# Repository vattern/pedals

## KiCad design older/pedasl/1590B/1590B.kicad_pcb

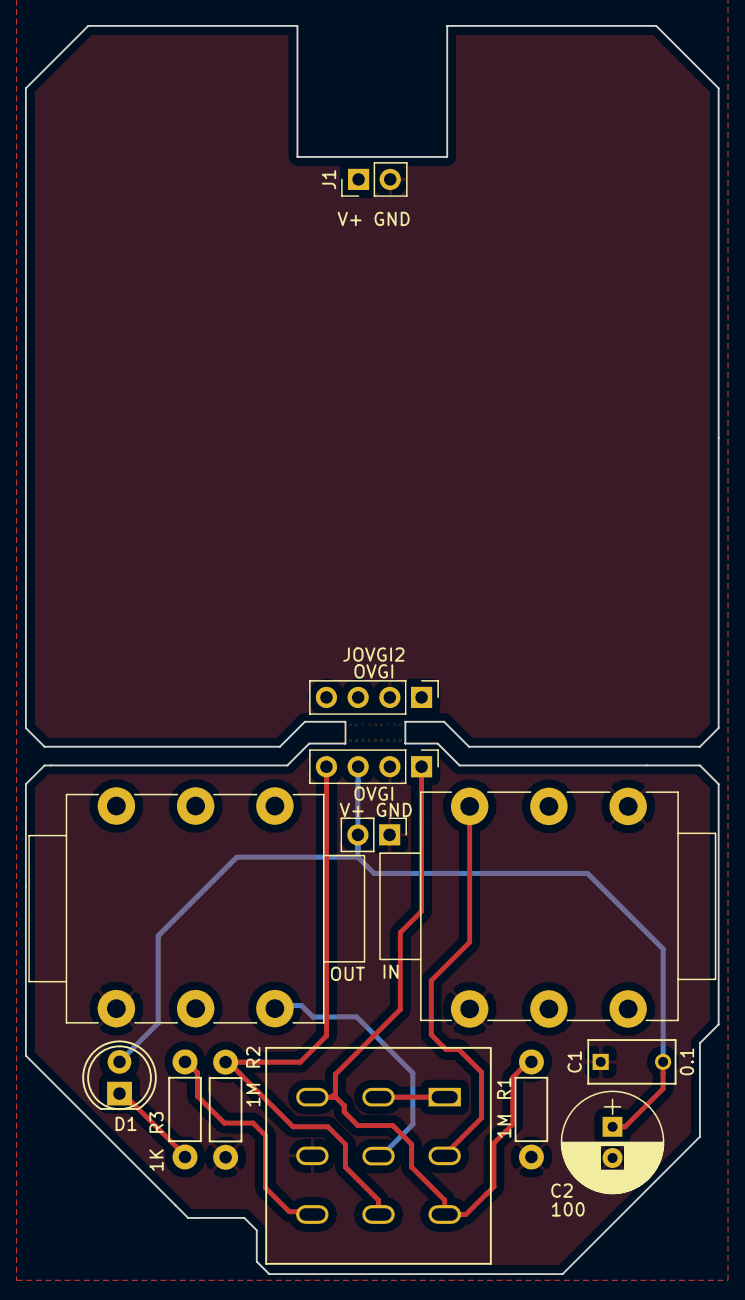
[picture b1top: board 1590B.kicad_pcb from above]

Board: 2 copper layers, 55.5 x 100.0 mm, 13 parts (0 on the bottom side), 9 nets.

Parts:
C1: 0.1; C_Rect_L7_W3.5_P5
C2: 100; CP_Radial_D8.0mm_P2.50mm
D1: LED; LED-5MM
J1, J4: V+ GND; Pin_Header_Straight_1x02_Pitch2.54mm
J2: IN; NMJ6HCD2
J3: OUT; NMJ6HCD2
JOVGI1, JOVGI2: OVGI; Pin_Header_Straight_1x04_Pitch2.54mm
R1, R2: 1M; Resistor_Horizontal_RM7mm
R3: 1K; Resistor_Horizontal_RM7mm
SW1: SW_3PDT; 3PDT-Footswitch

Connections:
+9V: C1.2, C2.1, D1.2, J1.1, J4.2, JOVGI1.3, JOVGI2.3
/I: JOVGI1.1, JOVGI2.1, R1.1, SW1.3, SW1.7
/O: JOVGI1.4, JOVGI2.4, R2.1, SW1.8
GND: C1.1, C2.2, J1.2, J2.1, J2.5, J3.1, J4.1, JOVGI1.2, JOVGI2.2, R1.2, R2.2, SW1.6
unnamed: D1.1, R3.1
unnamed: J2.2, SW1.4
unnamed: J3.2, SW1.5
unnamed: R3.2, SW1.9
unnamed: SW1.1, SW1.2

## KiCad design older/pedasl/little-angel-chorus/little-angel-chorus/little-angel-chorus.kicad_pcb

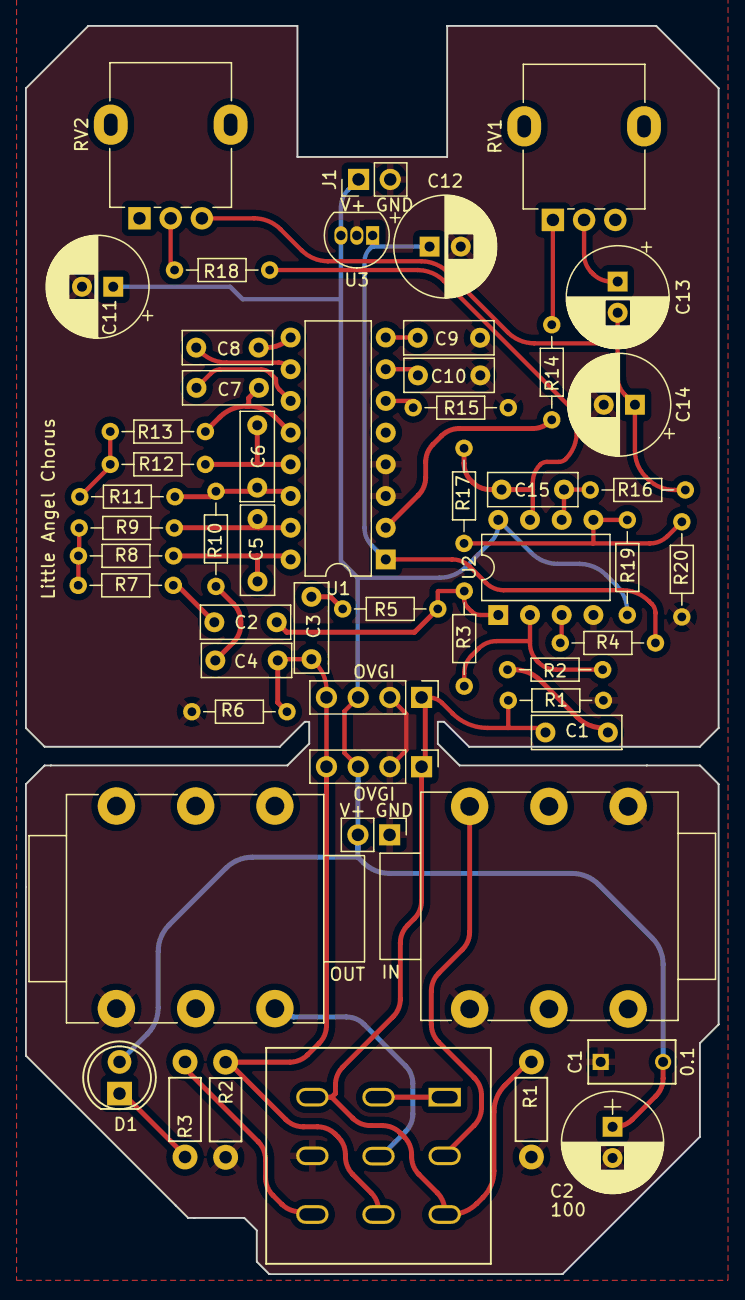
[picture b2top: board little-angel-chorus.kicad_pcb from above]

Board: 2 copper layers, 55.5 x 100.0 mm, 53 parts (0 on the bottom side), 38 nets.

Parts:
C1: 0.1; C_Rect_L7_W3.5_P5
C1#2, C2, C3, C4, C9, C10: 100nF; C_Disc_D7.0mm_W2.5mm_P5.00mm
C2#2: 100; CP_Radial_D8.0mm_P2.50mm
C5, C6: 1nF; C_Disc_D7.0mm_W2.5mm_P5.00mm
C7, C8, C15: 10nF; C_Disc_D7.0mm_W2.5mm_P5.00mm
C11: 100uF; CP_Radial_D8.0mm_P2.50mm
C12: 47uF; CP_Radial_D8.0mm_P2.50mm
C13, C14: 10uF; CP_Radial_D8.0mm_P2.50mm
D1: LED; LED-5MM
J1, J4: V+ GND; Pin_Header_Straight_1x02_Pitch2.54mm
J2: IN; NMJ6HCD2
J3: OUT; NMJ6HCD2
JOVGI1, JOVGI2: OVGI; Pin_Header_Straight_1x04_Pitch2.54mm
R1, R2: 1M; Resistor_Horizontal_RM7mm
R1#2, R3: 1M; R_Axial_DIN0204_L3.6mm_D1.6mm_P7.62mm_Horizontal
R2#2: 470k; R_Axial_DIN0204_L3.6mm_D1.6mm_P7.62mm_Horizontal
R3#2: 1K; Resistor_Horizontal_RM7mm
R4: 330k; R_Axial_DIN0204_L3.6mm_D1.6mm_P7.62mm_Horizontal
R5, R7, R8, R9, R10, R11, R12, R13: 10k; R_Axial_DIN0204_L3.6mm_D1.6mm_P7.62mm_Horizontal
R6, R19: 100k; R_Axial_DIN0204_L3.6mm_D1.6mm_P7.62mm_Horizontal
R14: 33k; R_Axial_DIN0204_L3.6mm_D1.6mm_P7.62mm_Horizontal
R15: 100R; R_Axial_DIN0204_L3.6mm_D1.6mm_P7.62mm_Horizontal
R16: 220K; R_Axial_DIN0204_L3.6mm_D1.6mm_P7.62mm_Horizontal
R17: 220k; R_Axial_DIN0204_L3.6mm_D1.6mm_P7.62mm_Horizontal
R18: 4k7; R_Axial_DIN0204_L3.6mm_D1.6mm_P7.62mm_Horizontal
R20: 47k; R_Axial_DIN0204_L3.6mm_D1.6mm_P7.62mm_Horizontal
RV1: 470K lin; Potentiometer_Alpha_RD901F-40-00D_Single_Vertical
RV2: 100k lin; Potentiometer_Alpha_RD901F-40-00D_Single_Vertical
SW1: SW_3PDT; 3PDT-Footswitch
U1: PT2399; DIP-16_W7.62mm
U2: NE5532; DIP-8_W7.62mm
U3: L78L05_TO92; TO-92_Inline

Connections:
+9V: C1.2, C2#2.1, C11.1, D1.2, J1.1, J4.2, JOVGI1.3, JOVGI2.3, R19.2, U2.8 (V+), U3.3 (VI)
GND: C1.1, C2#2.2, C9.1, C10.1, C11.2, C12.2, C14.2, J1.2, J2.1, J2.5, J3.1, J4.1, JOVGI1.2, JOVGI2.2, R1.2, R1#2.2, R2.2, R6.1, R15.1, R20.1, SW1.6, U1.3 (AGND), U1.4 (DGND), U2.4 (V-), U3.2 (GND)
unnamed: C1#2.2, R2#2.1
unnamed: C2.1, R7.1
unnamed: C2.2, R3.2, R5.1, U2.1
unnamed: C3.1, R5.2
unnamed: C4.1, R10.2
unnamed: C13.1, RV1.2
unnamed: C13.2, C14.1, R16.2, RV2.3
unnamed: C15.2, R17.2, R18.1, U2.7
unnamed: D1.1, R3#2.1
unnamed: J2.2, SW1.4
unnamed: J3.2, SW1.5
unnamed: R3#2.2, SW1.9
unnamed: R7.2, R8.2, R9.2
unnamed: R11.1, R12.1, R13.1
unnamed: R14.1, RV1.1
unnamed: R18.2, RV2.2
unnamed: SW1.1, SW1.2
unnamed: C9.2, U1.8 (CC0)
unnamed: C10.2, U1.7 (CC1)
unnamed: C5.1, R8.1, U1.16 (LPF1-IN)
unnamed: C5.2, R9.1, U1.15 (LPF1-OUT)
unnamed: C6.2, R12.2, U1.13 (LPF2-IN)
unnamed: C6.1, R10.1, R11.2, U1.14 (LPF2-OUT)
unnamed: C8.1, U1.10 (OP1-IN)
unnamed: C8.2, U1.9 (OP1-OUT)
unnamed: C7.2, U1.11 (OP2-IN)
unnamed: C7.1, R13.2, U1.12 (OP2-OUT)
unnamed: R14.2, U1.2 (REF)
unnamed: C12.1, R4.1, U1.1 (VCC), U3.1 (VO)
unnamed: R15.2, U1.6 (VCO)
unnamed: R4.2, U2.3 (+)
unnamed: R2#2.2, R3.1, U2.2 (-)
unnamed: R17.1, R19.1, R20.2, U2.5 (+)
unnamed: C15.1, R16.1, U2.6 (-)
/I: C1#2.1, JOVGI1.1, JOVGI2.1, R1.1, R1#2.1, SW1.3, SW1.7
/O: C3.2, C4.2, JOVGI1.4, JOVGI2.4, R2.1, R6.2, SW1.8

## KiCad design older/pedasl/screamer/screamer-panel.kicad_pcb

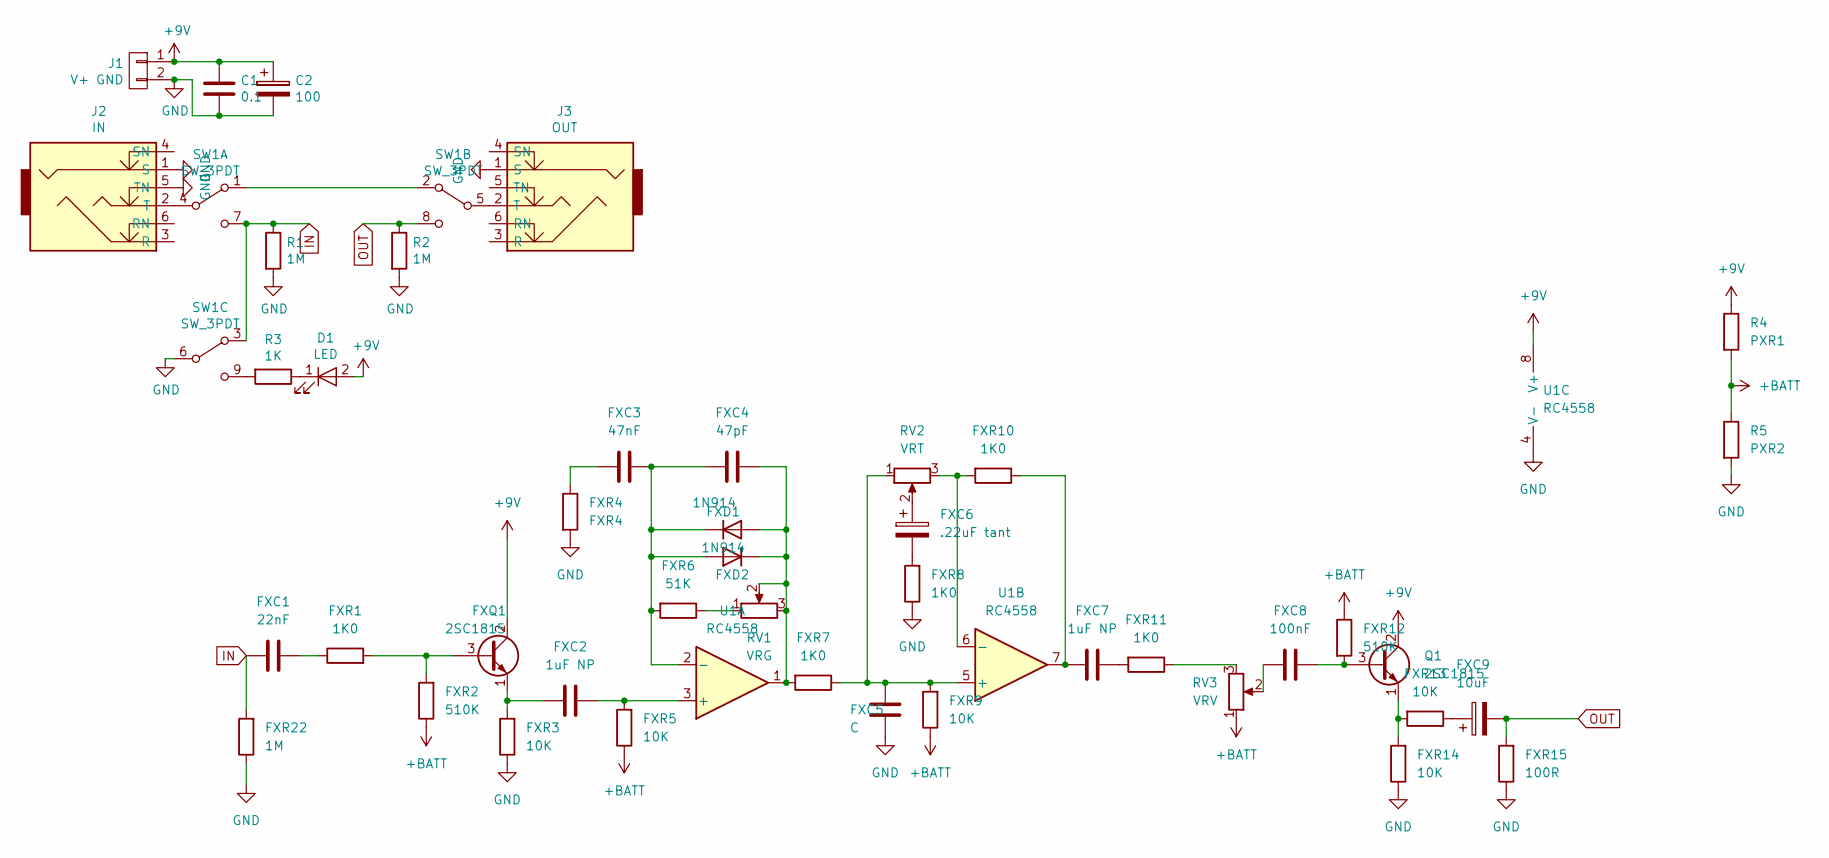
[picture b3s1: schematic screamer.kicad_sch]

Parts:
C1: 0.1; C_Rect_L7_W3.5_P5
C2: 100; CP_Radial_D8.0mm_P2.50mm
D1: LED; LED-5MM
FXC1: 22nF; C_Disc_D5.0mm_W2.5mm_P5.00mm
FXC2, FXC7: 1uF NP; C_Disc_D5.0mm_W2.5mm_P5.00mm
FXC3: 47nF; C_Disc_D5.0mm_W2.5mm_P5.00mm
FXC4: 47pF; C_Disc_D5.0mm_W2.5mm_P5.00mm
FXC5: C; C_Disc_D5.0mm_W2.5mm_P5.00mm
FXC6: .22uF tant; CP_Radial_D5.0mm_P2.50mm
FXC8: 100nF; C_Disc_D5.0mm_W2.5mm_P5.00mm
FXC9: 10uF; CP_Radial_D10.0mm_P5.00mm
FXD1, FXD2: 1N914; D_DO-35_SOD27_P7.62mm_Horizontal
FXQ1: 2SC1815; TO-92_Inline
FXR1, FXR7, FXR8, FXR10, FXR11: 1K0; R_Axial_DIN0207_L6.3mm_D2.5mm_P7.62mm_Horizontal
FXR2, FXR12: 510K; R_Axial_DIN0207_L6.3mm_D2.5mm_P7.62mm_Horizontal
FXR3, FXR5, FXR9, FXR13, FXR14: 10K; R_Axial_DIN0207_L6.3mm_D2.5mm_P7.62mm_Horizontal
FXR4: FXR4; R_Axial_DIN0207_L6.3mm_D2.5mm_P7.62mm_Horizontal
FXR6: 51K; R_Axial_DIN0207_L6.3mm_D2.5mm_P7.62mm_Horizontal
FXR15: 100R; R_Axial_DIN0207_L6.3mm_D2.5mm_P7.62mm_Horizontal
FXR22: 1M; R_Axial_DIN0207_L6.3mm_D2.5mm_P7.62mm_Horizontal
J1: V+ GND; Pin_Header_Straight_1x02_Pitch2.54mm
J2: IN; NMJ6HCD2
J3: OUT; NMJ6HCD2
Q1: 2SC1815; TO-92_Inline
R1, R2: 1M; Resistor_Horizontal_RM7mm
R3: 1K; Resistor_Horizontal_RM7mm
R4: PXR1; R_Axial_DIN0207_L6.3mm_D2.5mm_P7.62mm_Horizontal
R5: PXR2; R_Axial_DIN0207_L6.3mm_D2.5mm_P7.62mm_Horizontal
RV1: VRG; Potentiometer_Alps_RK09K_Single_Vertical
RV2: VRT; Potentiometer_Alps_RK09K_Single_Vertical
RV3: VRV; Potentiometer_Alps_RK09K_Single_Vertical
SW1: SW_3PDT; 3PDT-Footswitch
U1: RC4558; DIP-8_W7.62mm

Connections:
+9V: C1.2, C2.1, D1.2 (A), FXQ1.2 (C), J1.1, Q1.2 (C), R4.1, U1.8 (V+)
+BATT: FXR2.1, FXR5.1, FXR9.1, FXR12.1, R4.2, R5.1, RV3.1
GND: C1.1, C2.2, FXC5.1, FXR3.1, FXR4.2, FXR8.1, FXR14.1, FXR15.1, FXR22.1, J1.2, J2.1 (S), J2.5 (TN), J3.1 (S), R1.2, R2.2, R5.2, SW1.6 (B), U1.4 (V-)
IN: FXC1.1, FXR22.2, R1.1, SW1.3 (A), SW1.7 (C)
unnamed: D1.1 (K), R3.1
unnamed: FXC1.2, FXR1.1
unnamed: FXC2.1, FXQ1.1 (E), FXR3.2
unnamed: FXC2.2, FXR5.2, U1.3 (+)
unnamed: FXC3.1, FXR4.1
unnamed: FXC3.2, FXC4.1, FXD1.1 (K), FXD2.2 (A), FXR6.2, U1.2 (-)
unnamed: FXC4.2, FXD1.2 (A), FXD2.1 (K), FXR7.2, RV1.2, RV1.3, U1.1
unnamed: FXC5.2, FXR7.1, FXR9.2, RV2.1, U1.5 (+)
unnamed: FXC6.1, RV2.2
unnamed: FXC6.2, FXR8.2
unnamed: FXC7.1, FXR10.1, U1.7
unnamed: FXC7.2, FXR11.2
unnamed: FXC8.1, FXR12.2, Q1.3 (B)
unnamed: FXC8.2, RV3.2
unnamed: FXC9.1, FXR13.1
unnamed: FXQ1.3 (B), FXR1.2, FXR2.2
unnamed: FXR6.1, RV1.1
unnamed: FXR10.2, RV2.3, U1.6 (-)
unnamed: FXR11.1, RV3.3
unnamed: FXR13.2, FXR14.2, Q1.1 (E)
unnamed: J2.2 (T), SW1.4 (B)
unnamed: J3.2 (T), SW1.5 (B)
unnamed: R3.2, SW1.9 (C)
unnamed: SW1.1 (A), SW1.2 (A)
OUT: FXC9.2, FXR15.2, R2.1, SW1.8 (C)

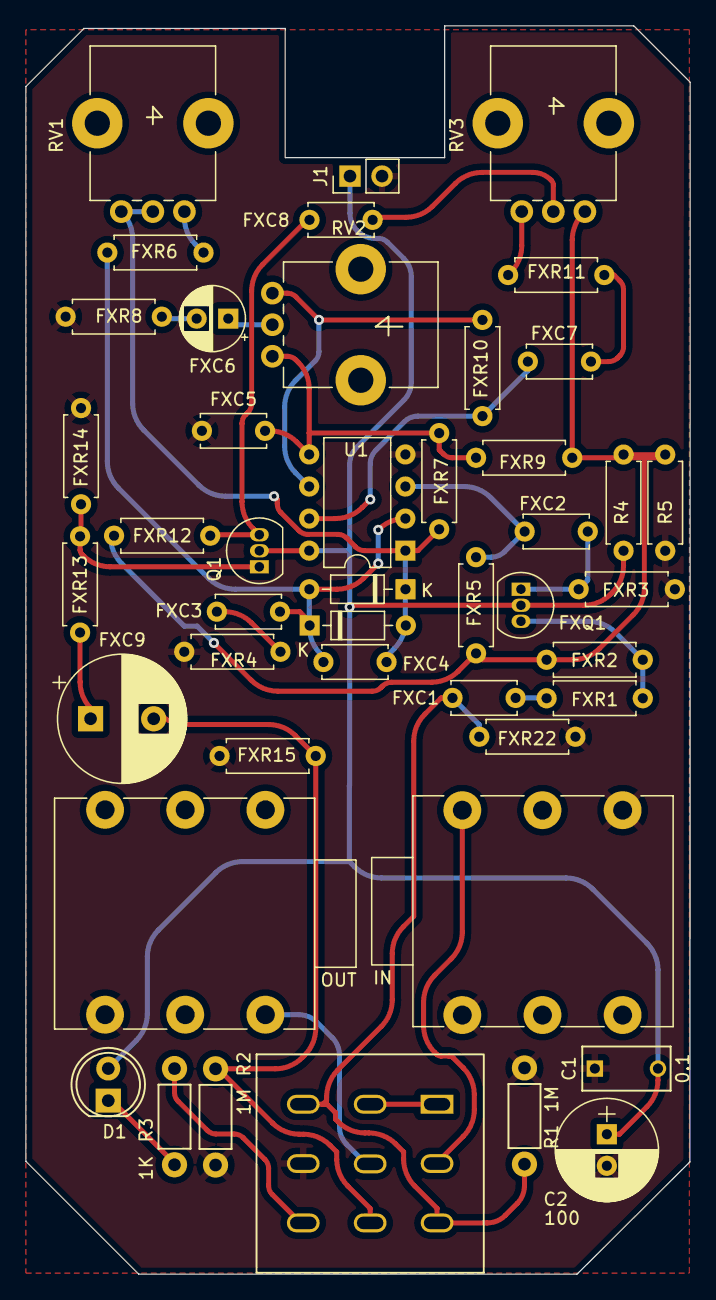
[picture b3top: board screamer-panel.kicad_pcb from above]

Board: 2 copper layers, 52.6 x 98.9 mm, 45 parts (0 on the bottom side), 29 nets.

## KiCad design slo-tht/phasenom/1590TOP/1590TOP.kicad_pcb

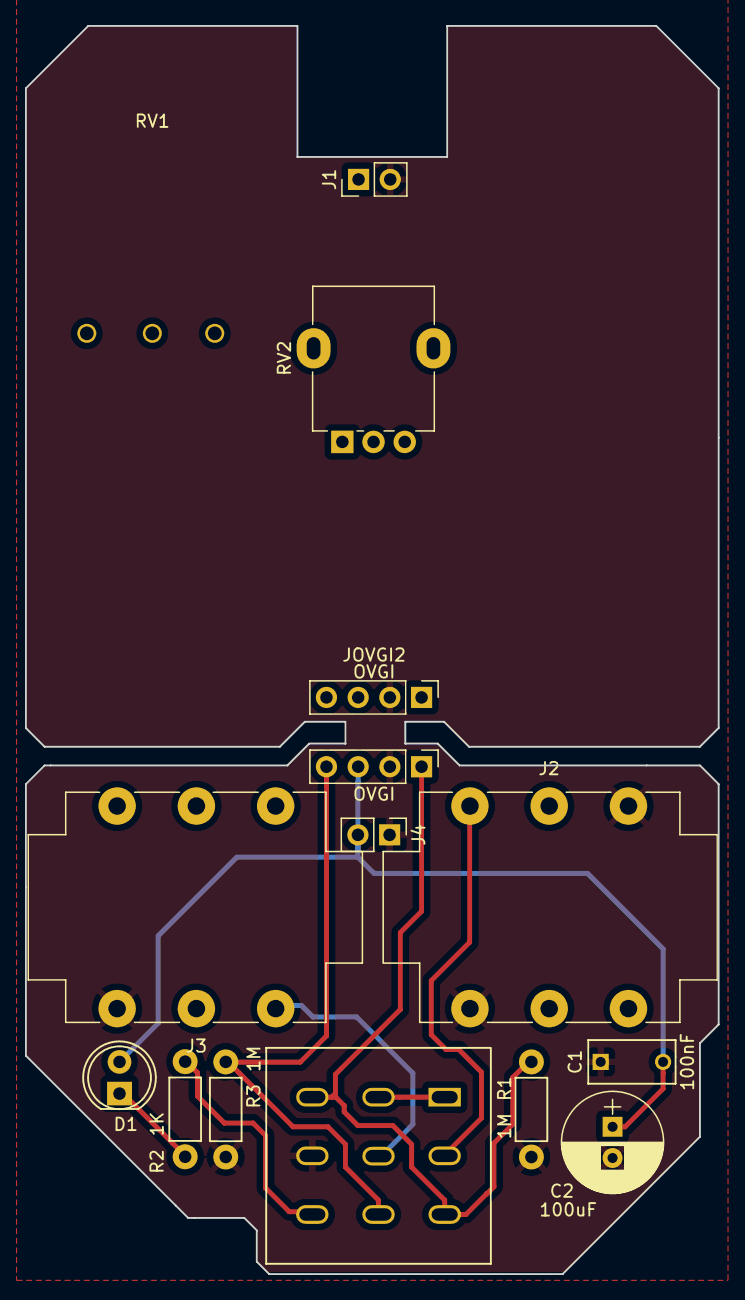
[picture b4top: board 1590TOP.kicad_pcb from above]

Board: 2 copper layers, 55.5 x 100.0 mm, 16 parts (0 on the bottom side), 9 nets.

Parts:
C1: 100nF; C_Rect_L7_W3.5_P5
C2: 100uF; CP_Radial_D8.0mm_P2.50mm
D1: LED; LED-5MM
J1, J4: V+ GND; PinHeader_1x02_P2.54mm_Vertical
J2, J3: NMJ6HCD2; Jack_6.35mm_Neutrik_NMJ6HCD2_Horizontal
JOVGI1, JOVGI2: OVGI; Pin_Header_Straight_1x04_Pitch2.54mm
N1: Housing; 1590B
R1, R3: 1M; Resistor_Horizontal_RM7mm
R2: 1K; Resistor_Horizontal_RM7mm
RV1: ALPHA-16mm; Potentiometer_ALPHA_RV16106N
RV2: ALPHA-9MM; Potentiometer_Alpha_RD901F-40-00D_Single_Vertical
SW1: SW_3PDT; 3PDT-Footswitch

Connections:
+9V: C1.2, C2.1, D1.2 (A), J1.1, J4.2, JOVGI1.3, JOVGI2.3
GND: C1.1, C2.2, J1.2, J2.S, J2.TN, J3.S, J4.1, JOVGI1.2, JOVGI2.2, R1.2, R3.2, SW1.6 (B)
I: JOVGI1.1, JOVGI2.1, R1.1, SW1.3 (A), SW1.7 (C)
unnamed: D1.1 (K), R2.1
unnamed: SW1.1 (A), SW1.2 (A)
unnamed: J2.T, SW1.4 (B)
unnamed: J3.T, SW1.5 (B)
unnamed: R2.2, SW1.9 (C)
O: JOVGI1.4, JOVGI2.4, R3.1, SW1.8 (C)

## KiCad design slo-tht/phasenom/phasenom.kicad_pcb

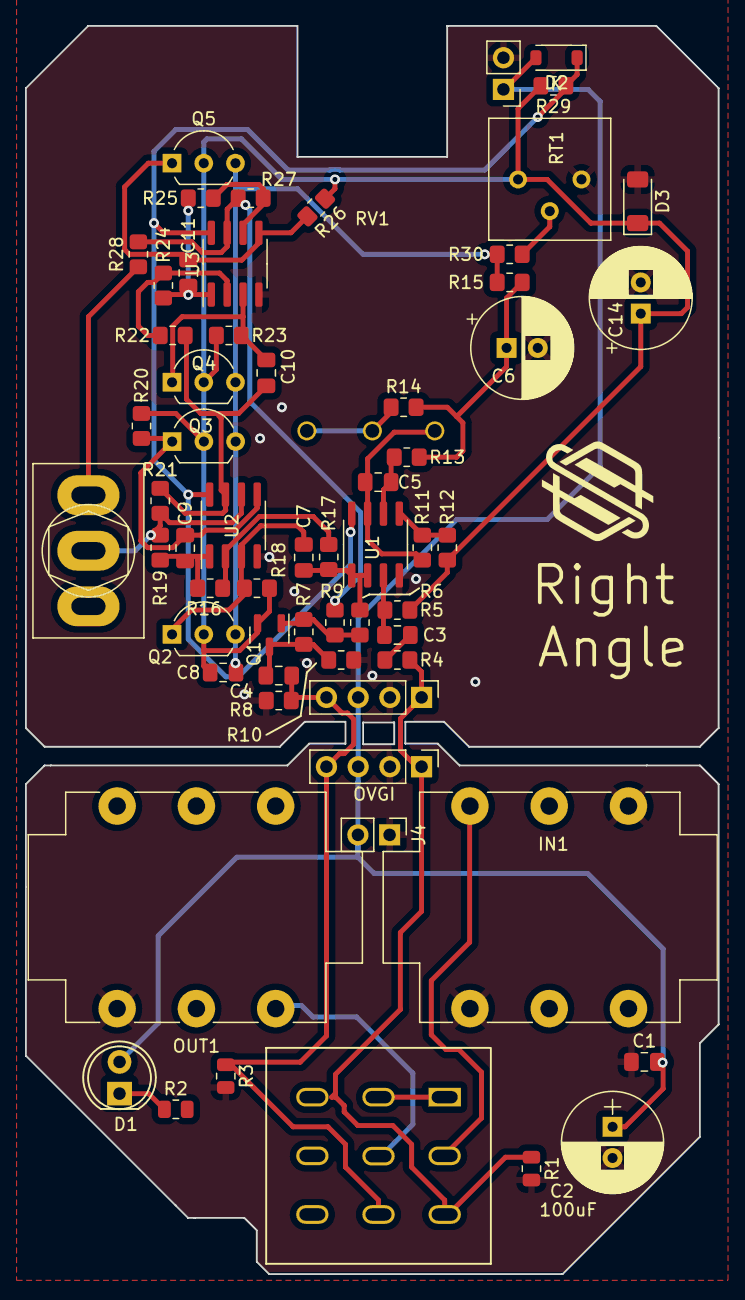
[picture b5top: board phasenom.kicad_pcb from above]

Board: 2 copper layers, 55.5 x 100.0 mm, 64 parts (0 on the bottom side), 35 nets.

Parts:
C1: 100nF; C_0805_2012Metric_Pad1.18x1.45mm_HandSolder
C2: 100uF; CP_Radial_D8.0mm_P2.50mm
C3, C5: 10n; C_0805_2012Metric_Pad1.18x1.45mm_HandSolder
C4, C7, C8, C9, C10, C11: 47n; C_0805_2012Metric_Pad1.18x1.45mm_HandSolder
C6: 15u; CP_Radial_D8.0mm_P2.50mm
C14: 22u; CP_Radial_D8.0mm_P2.50mm
D1: LED; LED-5MM
D2: 1N5817; D_SOD-123
D3: 5V1; D_MiniMELF
IN1: NMJ6HCD2; Jack_6.35mm_Neutrik_NMJ6HCD2_Horizontal
J1, J4: V+ GND; PinHeader_1x02_P2.54mm_Vertical
JOVGI1, JOVGI2: OVGI; Pin_Header_Straight_1x04_Pitch2.54mm
N1: Housing; 1590B
OUT1: NMJ6HCD2; Jack_6.35mm_Neutrik_NMJ6HCD2_Horizontal
Q1: MMBT3906; SOT-23
Q2, Q3, Q4, Q5: 2N5457; TO-92L_Inline_Wide
R1, R3: 1M; R_0805_2012Metric
R2: 1K; R_0805_2012Metric
R4, R16, R17, R19, R21, R22, R24, R25, R27, R29, R30: 10K; R_0805_2012Metric_Pad1.20x1.40mm_HandSolder
R5, R11: 470K; R_0805_2012Metric_Pad1.20x1.40mm_HandSolder
R6, R7, R8, R9, R12, R13: 150K; R_0805_2012Metric_Pad1.20x1.40mm_HandSolder
R10: 56K; R_0805_2012Metric_Pad1.20x1.40mm_HandSolder
R14: 4K7; R_0805_2012Metric_Pad1.20x1.40mm_HandSolder
R15: 3M9; R_0805_2012Metric_Pad1.20x1.40mm_HandSolder
R18, R20, R23, R26: 22K; R_0805_2012Metric_Pad1.20x1.40mm_HandSolder
R28: 27K; R_0805_2012Metric_Pad1.20x1.40mm_HandSolder
RT1: 250K; Potentiometer_Bourns_3386P_Vertical
RV1: 500KC; Potentiometer_ALPHA_RV16106N
SW2: SW_SPST; SW_Toggle_Blue_wSlots
SW99: SW_3PDT; 3PDT-Footswitch
U1, U2, U3: TL072; SOIC-8_3.9x4.9mm_P1.27mm

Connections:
+9V: C1.2, C2.1, D1.2 (A), D2.2 (A), J1.1, J4.2, JOVGI1.3, JOVGI2.3
GND: C1.1, C2.2, C6.2, C14.2, D3.2 (A), IN1.S, IN1.TN, J1.2, J4.1, JOVGI1.2, JOVGI2.2, OUT1.S, R1.2, R3.2, R8.1, R10.1, RT1.3, U1.4 (V-), U2.4 (V-), U3.4 (V-)
I: JOVGI1.1, JOVGI2.1, R1.1, R4.1, SW99.7 (C)
unnamed: C3.1, R4.2
unnamed: C5.1, R11.2, RV1.3, U1.7
unnamed: C6.1, R13.2, R14.2, R15.2
unnamed: C9.1, R16.2, R19.1, U2.1
unnamed: C10.1, R21.2, R22.1, U2.7
unnamed: C11.1, R24.2, R25.1, U3.1
unnamed: D1.1 (K), R2.1
unnamed: D2.1 (K), R29.1, U1.8 (V+), U2.8 (V+), U3.8 (V+)
unnamed: Q1.1 (B), R6.2, R7.1, R9.2
unnamed: C4.1, Q1.3 (C), R7.2, R10.2
unnamed: C7.2, Q2.1 (D), R18.2, U2.3 (+)
unnamed: C9.2, Q3.1 (D), R20.2, U2.5 (+)
unnamed: C10.2, Q4.1 (D), R23.2, U3.3 (+)
unnamed: C11.2, Q5.1 (D), R26.2, U3.5 (+)
unnamed: R14.1, RV1.1, RV1.2
unnamed: R9.1, R27.2, R28.1, U3.7
unnamed: R30.1, RT1.2
unnamed: R28.2, SW2.1 (A)
unnamed: R19.2, R21.1, SW2.2 (B), U2.6 (-)
unnamed: SW99.1 (A), SW99.2 (A)
unnamed: IN1.T, SW99.4 (B)
unnamed: OUT1.T, SW99.5 (B)
unnamed: C3.2, R5.1, U1.3 (+)
unnamed: C7.1, R6.1, R17.1, U1.1, U1.2 (-)
unnamed: R11.1, R12.2, U1.5 (+)
unnamed: C5.2, R13.1, U1.6 (-)
unnamed: R16.1, R17.2, U2.2 (-)
unnamed: R22.2, R24.1, U3.2 (-)
unnamed: R25.2, R27.1, U3.6 (-)
O: C4.2, JOVGI1.4, JOVGI2.4, R3.1, R8.2, SW99.8 (C)
VB: C8.1, C14.1, D3.1 (K), Q1.2 (E), Q2.2 (S), Q3.2 (S), Q4.2 (S), Q5.2 (S), R5.2, R12.1, R18.1, R20.1, R23.1, R26.1, R29.2, RT1.1
VR: C8.2, Q2.3 (G), Q3.3 (G), Q4.3 (G), Q5.3 (G), R15.1, R30.2
